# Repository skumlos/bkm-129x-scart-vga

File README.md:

A SCART/VGA BKM-129X compatible board

Revision F

Should be able to be created at ~$40, with the ADG1611BRUZ being the most expensive component.
Note that the DG1411EEQ is pin-compatible, with a slightly higher Ron.

This requires an Arduino Nano v3 *or* the ATMEGA328PB mounted, which is then loaded with the
latest BKM-129X-MCU code from https://github.com/skumlos/bkm-129x-mcu

The middle 4PDT switch selects SCART or VGA. The top switch selects if the VGA sync signal should combine HV to CSYNC
or just feed CSYNC on. Note that CSYNC should be 75 Ohm level.

You are welcome to clone, produce and sell hardware based on this. Please keep changes and so on open source.

I (finally) upgraded to Kicad 5 during this, so if there are any library issues or whatnot,
let me know, as this was converted from 4.7 to 5.1 automagically.
 
Cool kids give credit where due.

---------

Programming the onboard ATMEGA328PB is a little different than when using a pre-made Arduino board.
The reason for this is that the fuses of the ATMEGA aren't set when the MCU leaves the factory.
Thus to program it, you will need ATMEGA328PB support in the Arduino IDE. The easiest way is to
install the MiniCore board support package (through the Boards Manager), for installation
check the "How to install" at https://github.com/MCUdude/MiniCore.
When MiniCore is available,  select the ATMEGA328 under MiniCore in the board menu, then select
"External 16 MHz" in Clock, disable BOD, select ATMEGA328PB in Variant, select No bootloader.
Then press "Burn bootloader" (assuming your programmer and so on is already setup). This will
program the fuses. Last, upload the sketch by pressing "Upload using programmer". If you don't
do this, nothing will work, because the MCU won't know how to use the external clock and so on.

---------

Should be compatible with basically all monitors that accept the original BKM-129X

Check the MCU code for verified compatibility.

---------

Board revision history:

F: Add option for LD1117 LDO, update to Kicad 5 footprints, minor cosmetical changes

E: Change backplane connector pads to larger ones. Includes silkscreen fix from user 'bodgit', thanks!

D1: Connect VGA pin 5 to GND, fix MIC3490-3.3 -> MIC3490-5.0

D: Remove VGA pin 9 connectivity to GND and leave unconnected.

C: Fixed THS7374 filter bypass, moved sync switch to front.

B: Fixed audio routing

A: Initial version

---------

Copyright © 2022 Martin Hejnfelt <martin@hejnfelt.com>
This work is free. You can redistribute it and/or modify it under the
terms of the Do What The Fuck You Want To Public License, Version 2,
as published by Sam Hocevar. See the LICENSE file for more details.

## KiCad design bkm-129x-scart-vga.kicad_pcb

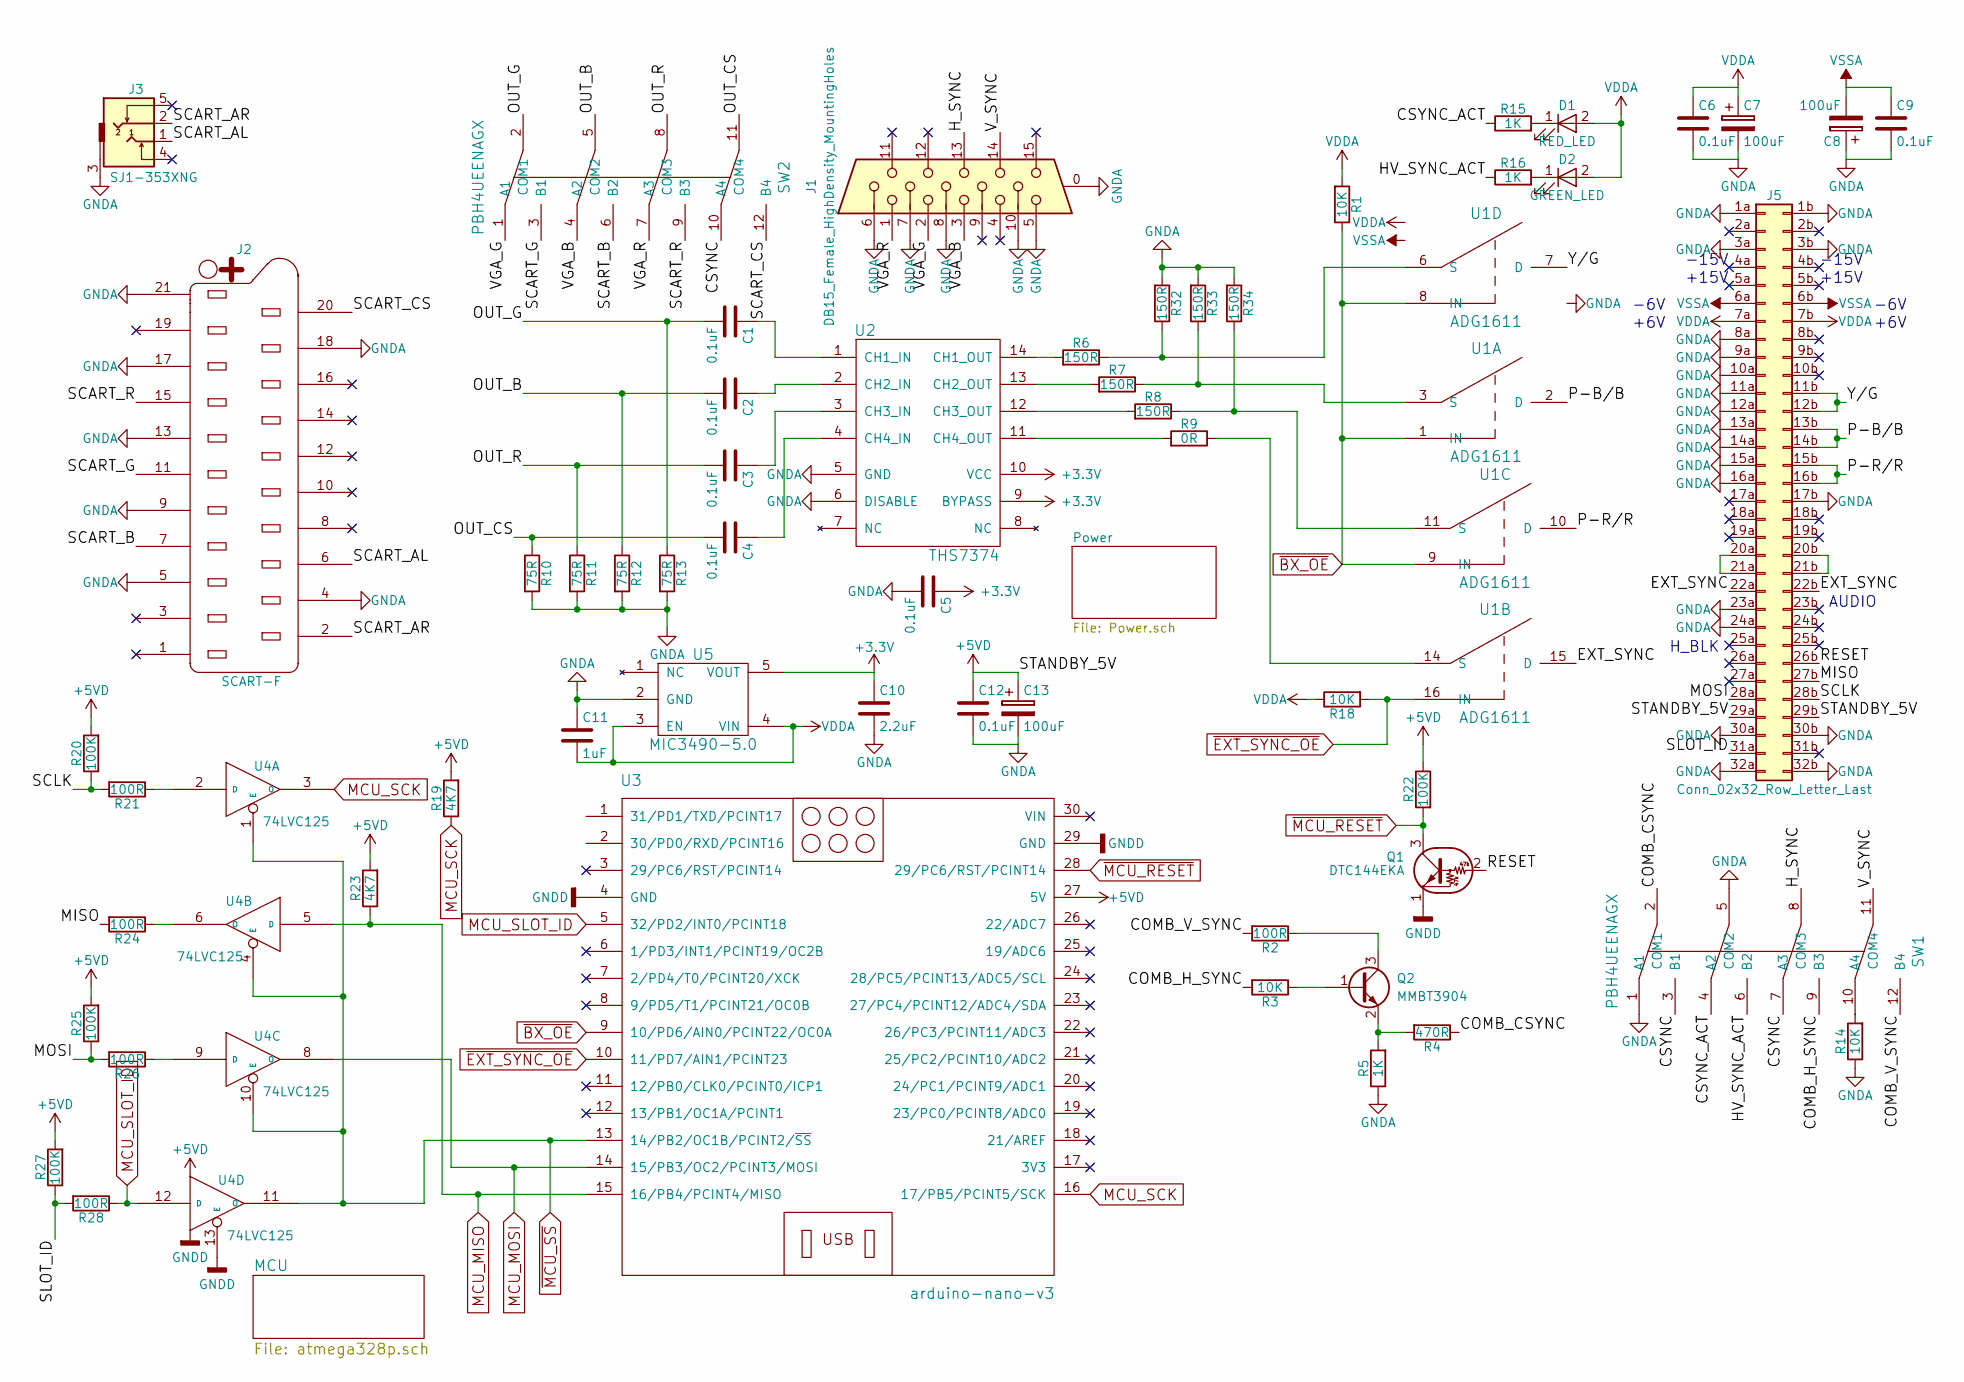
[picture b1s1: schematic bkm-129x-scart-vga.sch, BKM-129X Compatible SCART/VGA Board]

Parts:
C1, C2, C3, C4, C5, C6, C9, C12: 0.1uF; C_0805_2012Metric_Pad1.18x1.45mm_HandSolder
C7, C8, C13: 100uF; CP_Elec_6.3x5.3
C10: 2.2uF; C_0805_2012Metric_Pad1.18x1.45mm_HandSolder
C11: 1uF; C_0805_2012Metric_Pad1.18x1.45mm_HandSolder
D1: RED_LED; D_0805_2012Metric_Pad1.15x1.40mm_HandSolder
D2: GREEN_LED; D_0805_2012Metric_Pad1.15x1.40mm_HandSolder
J1: DB15_Female_HighDensity_MountingHoles; HD15-VGA
J2: SCART-F; NINIGI-SCART-RA
J3: SJ1-353XNG
J5: Conn_02x32_Row_Letter_Last; STANDARD-PIN-64P-RA
Q1: DTC144EKA; SC-59_Handsoldering
Q2: MMBT3904; SOT-23_Handsoldering
R1, R3, R14, R18: 10K; R_0805_2012Metric_Pad1.20x1.40mm_HandSolder
R2, R21, R24, R26, R28: 100R; R_0805_2012Metric_Pad1.20x1.40mm_HandSolder
R4: 470R; R_0805_2012Metric_Pad1.20x1.40mm_HandSolder
R5, R15, R16: 1K; R_0805_2012Metric_Pad1.20x1.40mm_HandSolder
R6, R7, R8, R32, R33, R34: 150R; R_0805_2012Metric_Pad1.20x1.40mm_HandSolder
R9: 0R; R_0805_2012Metric_Pad1.20x1.40mm_HandSolder
R10, R11, R12, R13: 75R; R_0805_2012Metric_Pad1.20x1.40mm_HandSolder
R19, R23: 4K7; R_0805_2012Metric_Pad1.20x1.40mm_HandSolder
R20, R22, R25, R27: 100K; R_0805_2012Metric_Pad1.20x1.40mm_HandSolder
SW1, SW2: PBH4UEENAGX; PBH4UEE
U1: ADG1611; TSSOP-16_4.4x5mm_P0.65mm
U2: THS7374; TSSOP-14_4.4x5mm_P0.65mm
U3: arduino-nano-v3
U4: 74LVC125; TSSOP-14_4.4x5mm_P0.65mm
U5: MIC3490-5.0; SOT-23-5_HandSoldering

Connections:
+3V3: C5.1, C10.1, U2.9 (BYPASS), U2.10 (VCC), U5.5 (VOUT); also elsewhere on the board
+5VD: C12.1, C13.1, J5.29a, J5.29b, R19.2, R20.2, R22.1, R23.2, R25.2, R27.2, U3.27 (5V), U4.14 (VCC); also elsewhere on the board
/COMB_CSYNC: R4.1, SW1.2 (COM1)
/COMB_H_SYNC: R3.2, SW1.9 (B3)
/COMB_V_SYNC: R2.2, SW1.12 (B4)
/CSYNC: SW1.3 (B1), SW1.7 (A3), SW2.10 (A4)
/CSYNC_ACT: R15.1, SW1.4 (A2)
/EXT_SYNC: J5.22a, J5.22b, U1.15 (D)
/HV_SYNC_ACT: R16.1, SW1.6 (B2)
/H_SYNC: J1.13, SW1.8 (COM3)
/MISO: J5.27b, R24.2
/MOSI: J5.28a, R25.1, R26.2
/OUT_B: C2.2, R12.1, SW2.5 (COM2)
/OUT_CS: C4.2, R10.1, SW2.11 (COM4)
/OUT_G: C1.2, R13.1, SW2.2 (COM1)
/OUT_R: C3.2, R11.1, SW2.8 (COM3)
/P-B/B: J5.13b, J5.14b, U1.2 (D)
/P-R/R: J5.15b, J5.16b, U1.10 (D)
/RESET: J5.26b, Q1.2 (B)
/SCART_AL: J2.6, J3.1
/SCART_AR: J2.2, J3.2
/SCART_B: J2.7, SW2.6 (B2)
/SCART_CS: J2.20, SW2.12 (B4)
/SCART_G: J2.11, SW2.3 (B1)
/SCART_R: J2.15, SW2.9 (B3)
/SCLK: J5.28b, R20.1, R21.2
/SLOT_ID: J5.31a, R27.1, R28.2
/VGA_B: J1.3, SW2.4 (A2)
/VGA_G: J1.2, SW2.1 (A1)
/VGA_R: J1.1, SW2.7 (A3)
/V_SYNC: J1.14, SW1.11 (COM4)
/Y/G: J5.11b, J5.12b, U1.7 (D)
MCU_MISO: R23.1, U3.15 (16/PB4/PCINT4/MISO), U4.5 (D); also elsewhere on the board
MCU_MOSI: U3.14 (15/PB3/OC2/PCINT3/MOSI), U4.8 (O); also elsewhere on the board
MCU_SCK: R19.1, U3.16 (17/PB5/PCINT5/SCK), U4.3 (O); also elsewhere on the board
MCU_SLOT_ID: R28.1, U3.5 (32/PD2/INT0/PCINT18), U4.12 (D); also elsewhere on the board
unnamed: C1.1, U2.1 (CH1_IN)
unnamed: C2.1, U2.2 (CH2_IN)
unnamed: C3.1, U2.3 (CH3_IN)
unnamed: C4.1, U2.4 (CH4_IN)
unnamed: D1.1 (K), R15.2
unnamed: D2.1 (K), R16.2
unnamed: J5.20a, J5.21a
unnamed: J5.20b, J5.21b
unnamed: Q2.1 (B), R3.1
unnamed: Q2.2 (E), R4.2, R5.2
unnamed: Q2.3 (C), R2.1
unnamed: R6.2, U2.14 (CH1_OUT)
unnamed: R7.2, U2.13 (CH2_OUT)
unnamed: R8.2, U2.12 (CH3_OUT)
unnamed: R9.1, U1.14 (S)
unnamed: R9.2, U2.11 (CH4_OUT)
unnamed: R14.2, SW1.10 (A4)
unnamed: R21.1, U4.2 (D)
unnamed: R24.1, U4.6 (O)
unnamed: R26.1, U4.9 (D)
unnamed: R6.1, R32.1, U1.6 (S)
unnamed: R7.1, R33.1, U1.3 (S)
unnamed: R8.1, R34.1, U1.11 (S)
VDD: C6.1, C7.1, C11.2, D1.2 (A), D2.2 (A), J5.7a, J5.7b, R1.2, R18.1, U1.13 (VDD), U5.3 (EN), U5.4 (VIN); also elsewhere on the board
VSS: C8.2, C9.1, J5.6a, J5.6b, U1.4 (VSS)
~BX_OE: R1.1, U1.1 (IN), U1.8 (IN), U1.9 (IN), U3.9 (10/PD6/AIN0/PCINT22/OC0A); also elsewhere on the board
~EXT_SYNC_OE: R18.2, U1.16 (IN), U3.10 (11/PD7/AIN1/PCINT23); also elsewhere on the board
~MCU_RESET: Q1.3 (C), R22.2, U3.28 (29/PC6/RST/PCINT14); also elsewhere on the board
~MCU_SS: U3.13 (14/PB2/OC1B/PCINT2/~SS), U4.1 (E), U4.4 (E), U4.10 (E), U4.11 (O); also elsewhere on the board

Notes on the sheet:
-15V
+15V
-6V
+6V
AUDIO
H_BLK

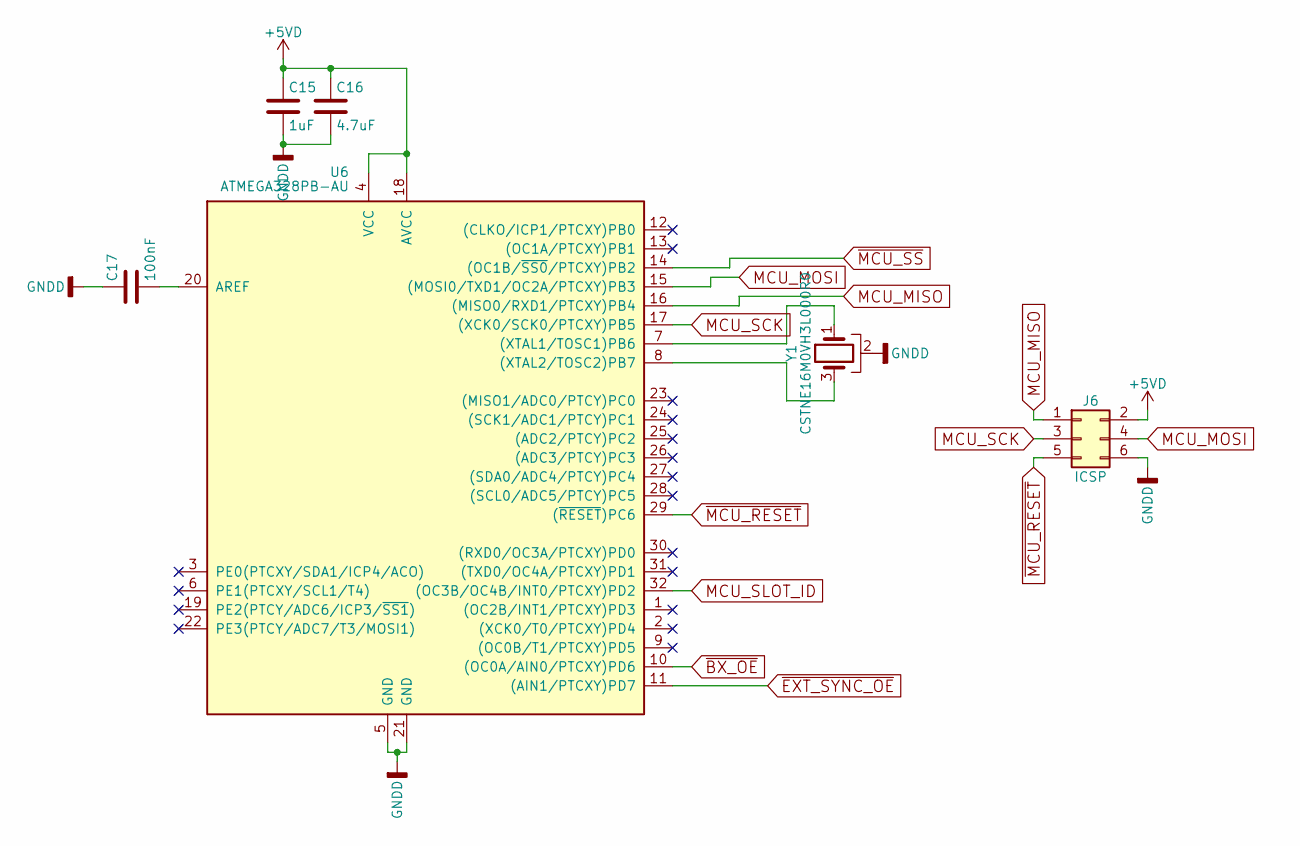
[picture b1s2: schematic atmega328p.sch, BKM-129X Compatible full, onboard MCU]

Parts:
C15: 1uF; C_0805_2012Metric_Pad1.18x1.45mm_HandSolder
C16: 4.7uF; C_0805_2012Metric_Pad1.18x1.45mm_HandSolder
C17: 100nF; C_0805_2012Metric_Pad1.18x1.45mm_HandSolder
J6: ICSP; Pin_Header_Straight_2x03_Pitch2.54mm
U6: ATMEGA328PB-AU; TQFP-32_7x7mm_P0.8mm
Y1: CSTNE16M0VH3L000R0; Resonator_SMD_muRata_CSTxExxV-3Pin_3.0x1.1mm

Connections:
+5VD: C15.1, C16.1, J6.2, U6.4 (VCC), U6.18 (AVCC); also elsewhere on the board
MCU_MISO: J6.1, U6.16 ((MISO0/RXD1/PTCXY)PB4); also elsewhere on the board
MCU_MOSI: J6.4, U6.15 ((MOSI0/TXD1/OC2A/PTCXY)PB3); also elsewhere on the board
MCU_SCK: J6.3, U6.17 ((XCK0/SCK0/PTCXY)PB5); also elsewhere on the board
MCU_SLOT_ID: U6.32 ((OC3B/OC4B/INT0/PTCXY)PD2); also elsewhere on the board
unnamed: C17.2, U6.20 (AREF)
unnamed: U6.7 ((XTAL1/TOSC1)PB6), Y1.1
unnamed: U6.8 ((XTAL2/TOSC2)PB7), Y1.3
~BX_OE: U6.10 ((OC0A/AIN0/PTCXY)PD6); also elsewhere on the board
~EXT_SYNC_OE: U6.11 ((AIN1/PTCXY)PD7); also elsewhere on the board
~MCU_RESET: J6.5, U6.29 ((~RESET~)PC6); also elsewhere on the board
~MCU_SS: U6.14 ((OC1B/~SS0~/PTCXY)PB2); also elsewhere on the board

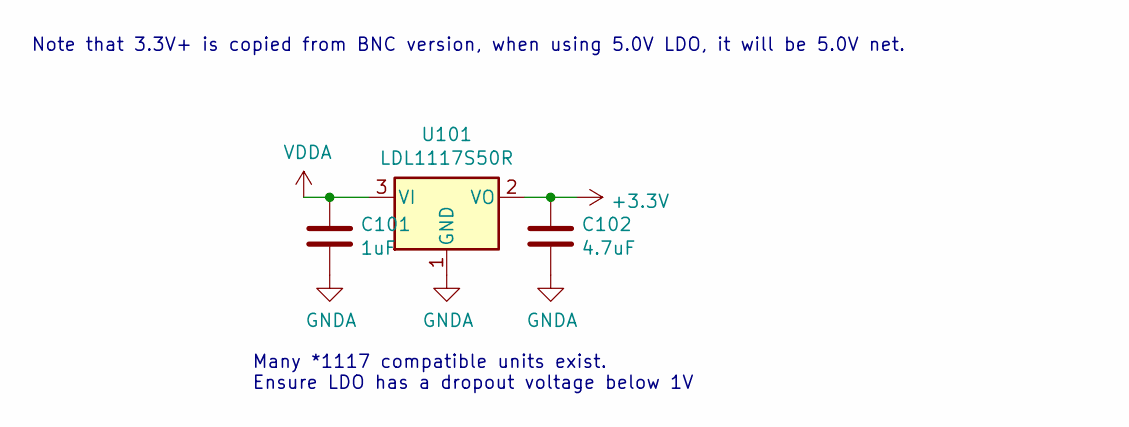
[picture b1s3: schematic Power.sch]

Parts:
C101: 1uF; C_0805_2012Metric_Pad1.18x1.45mm_HandSolder
C102: 4.7uF; C_0805_2012Metric_Pad1.18x1.45mm_HandSolder
U101: LDL1117S50R; SOT-223-3_TabPin2

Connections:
+3V3: C102.1, U101.2 (VO); also elsewhere on the board
VDD: C101.1, U101.3 (VI); also elsewhere on the board

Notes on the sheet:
Note that 3.3V+ is copied from BNC version, when using 5.0V LDO, it will be 5.0V net.
Many *1117 compatible units exist. Ensure LDO has a dropout voltage below 1V

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
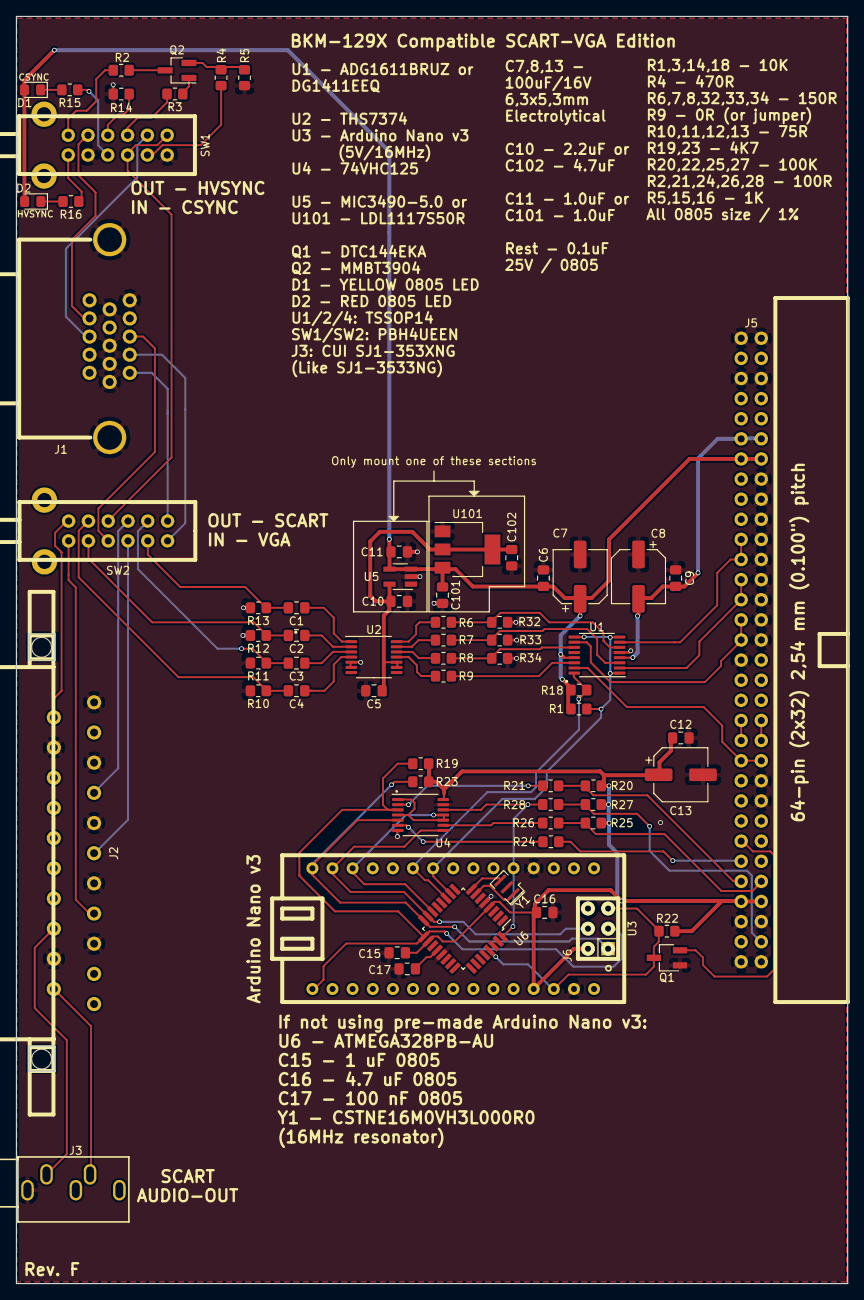
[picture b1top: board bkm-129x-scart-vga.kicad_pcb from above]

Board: 2 copper layers, 105.0 x 160.0 mm, 67 parts (0 on the bottom side), 69 nets.

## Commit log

2021-04-04 Rev. C. Move to Kicad 5
2021-04-04 Add plot
2021-04-04 Fixed formatting of revision section in readme
2021-05-09 Rev. D
2021-08-02 Correct U5 part number
    Schematic says it's the -3.3 version.
2021-08-09 Rev. D1
2021-09-08 Fix R9 value on silkscreen
    Schematic says R9 is 0Ω, silkscreen says it's 150Ω. Also condense the
    remaining 150Ω resistors into one line.
2021-09-08 Rev. E
2022-05-19 Update to rev. F
2022-05-19 Added missing new sheet
2022-05-20 Fixed 1117 PN to LDL1117S50R
